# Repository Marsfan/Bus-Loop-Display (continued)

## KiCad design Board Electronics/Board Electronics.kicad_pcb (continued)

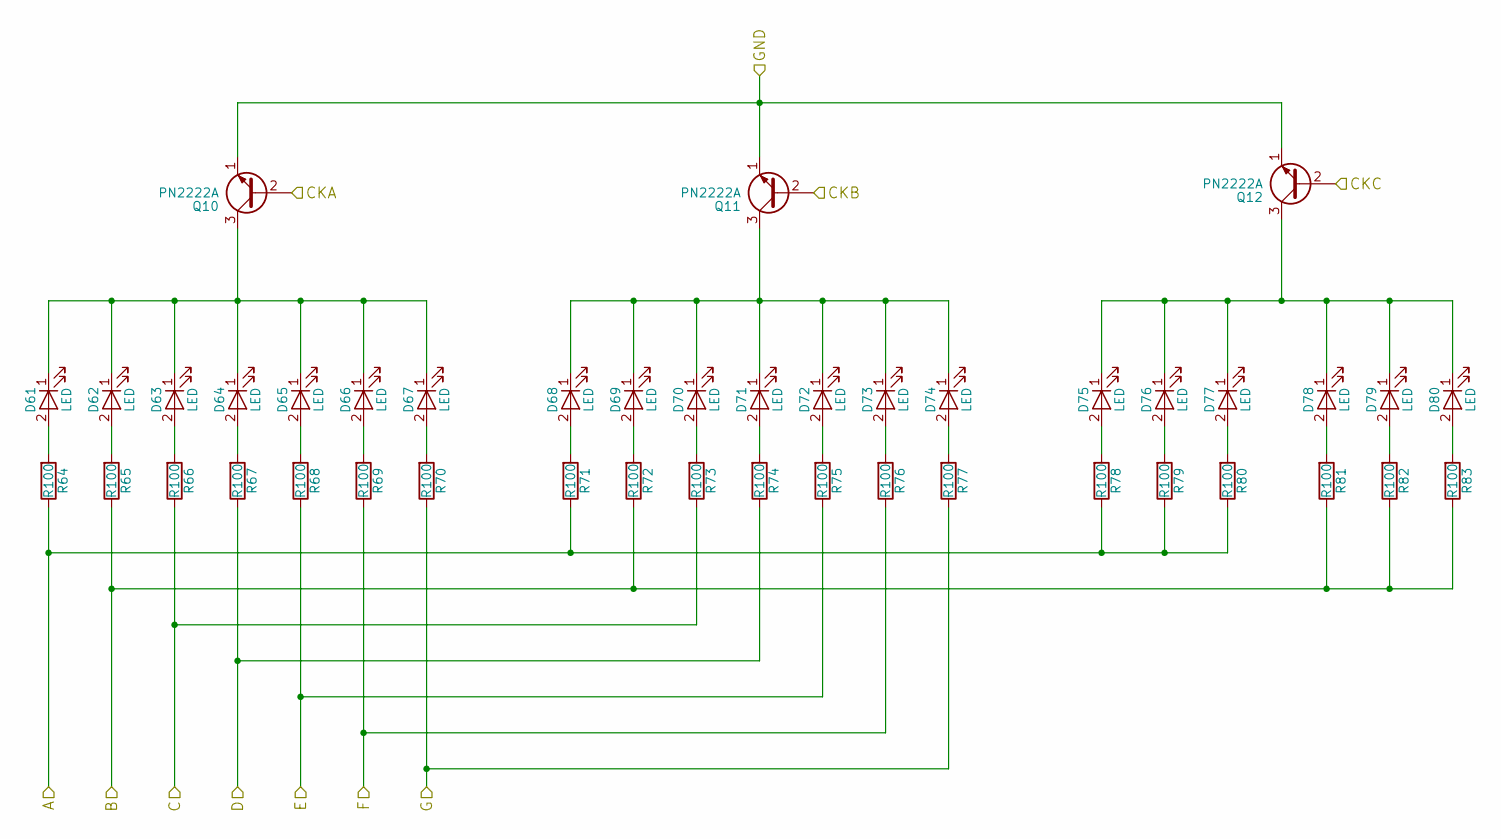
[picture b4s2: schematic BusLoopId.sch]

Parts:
D1, D2, D3, D4, D5, D6, D7, D8, D9, D10, D11, D12, D13, D14, D15, D16, D17, D18, D19, D20: LED; LED_D5.0mm
Q1, Q2, Q3: PN2222A; TO-92_Inline_Narrow_Oval
R4, R5, R6, R7, R8, R9, R10, R11, R12, R13, R14, R15, R16, R17, R18, R19, R20, R21, R22, R23: R100; R_Axial_DIN0309_L9.0mm_D3.2mm_P12.70mm_Horizontal

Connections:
/CKA: Q1.2 (B); also elsewhere on the board
/CKB: Q2.2 (B); also elsewhere on the board
/CKC: Q3.2 (B); also elsewhere on the board
/GND: Q1.1 (E), Q2.1 (E), Q3.1 (E); also elsewhere on the board
/Route 1/A: R4.1, R11.1, R18.1, R19.1, R20.1; also elsewhere on the board
/Route 1/B: R5.1, R12.1, R21.1, R22.1, R23.1; also elsewhere on the board
/Route 1/C: R6.1, R13.1; also elsewhere on the board
/Route 1/D: R7.1, R14.1; also elsewhere on the board
/Route 1/E: R8.1, R15.1; also elsewhere on the board
/Route 1/F: R9.1, R16.1; also elsewhere on the board
/Route 1/G: R10.1, R17.1; also elsewhere on the board
unnamed: D1.1 (K), D2.1 (K), D3.1 (K), D4.1 (K), D5.1 (K), D6.1 (K), D7.1 (K), Q1.3 (C)
unnamed: D1.2 (A), R4.2
unnamed: D2.2 (A), R5.2
unnamed: D3.2 (A), R6.2
unnamed: D4.2 (A), R7.2
unnamed: D5.2 (A), R8.2
unnamed: D6.2 (A), R9.2
unnamed: D7.2 (A), R10.2
unnamed: D8.2 (A), R11.2
unnamed: D9.2 (A), R12.2
unnamed: D8.1 (K), D9.1 (K), D10.1 (K), D11.1 (K), D12.1 (K), D13.1 (K), D14.1 (K), Q2.3 (C)
unnamed: D10.2 (A), R13.2
unnamed: D11.2 (A), R14.2
unnamed: D12.2 (A), R15.2
unnamed: D13.2 (A), R16.2
unnamed: D14.2 (A), R17.2
unnamed: D15.1 (K), D16.1 (K), D17.1 (K), D18.1 (K), D19.1 (K), D20.1 (K), Q3.3 (C)
unnamed: D15.2 (A), R18.2
unnamed: D16.2 (A), R19.2
unnamed: D17.2 (A), R20.2
unnamed: D18.2 (A), R21.2
unnamed: D19.2 (A), R22.2
unnamed: D20.2 (A), R23.2

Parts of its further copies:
D21, D22, D23, D24, D25, D26, D27, D28, D29, D30, D31, D32, D33, D34, D35, D36, D37, D38, D39, D40, D41, D42, D43, D44, D45, D46, D47, D48, D49, D50, D51, D52, D53, D54, D55, D56, D57, D58, D59, D60, D61, D62, D63, D64, D65, D66, D67, D68, D69, D70, D71, D72, D73, D74, D75, D76, D77, D78, D79, D80, D81, D82, D83, D84, D85, D86, D87, D88, D89, D90, D91, D92, D93, D94, D95, D96, D97, D98, D99, D100, D101, D102, D103, D104, D105, D106, D107, D108, D109, D110, D111, D112, D113, D114, D115, D116, D117, D118, D119, D120: LED; LED_D5.0mm
Q4, Q5, Q6, Q7, Q8, Q9, Q10, Q11, Q12, Q13, Q14, Q15, Q16, Q17, Q18: PN2222A; TO-92_Inline_Narrow_Oval
R24, R25, R26, R27, R28, R29, R30, R31, R32, R33, R34, R35, R36, R37, R38, R39, R40, R41, R42, R43, R44, R45, R46, R47, R48, R49, R50, R51, R52, R53, R54, R55, R56, R57, R58, R59, R60, R61, R62, R63, R64, R65, R66, R67, R68, R69, R70, R71, R72, R73, R74, R75, R76, R77, R78, R79, R80, R81, R82, R83, R84, R85, R86, R87, R88, R89, R90, R91, R92, R93, R94, R95, R96, R97, R98, R99, R100, R101, R102, R103, R104, R105, R106, R107, R108, R109, R110, R111, R112, R113, R114, R115, R116, R117, R118, R119, R120, R121, R122, R123: R100; R_Axial_DIN0309_L9.0mm_D3.2mm_P12.70mm_Horizontal

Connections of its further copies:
/CKA: Q4.2 (B), Q7.2 (B), Q10.2 (B), Q13.2 (B), Q16.2 (B); also elsewhere on the board
/CKB: Q5.2 (B), Q8.2 (B), Q11.2 (B), Q14.2 (B), Q17.2 (B); also elsewhere on the board
/CKC: Q6.2 (B), Q9.2 (B), Q12.2 (B), Q15.2 (B), Q18.2 (B); also elsewhere on the board
/GND: Q4.1 (E), Q5.1 (E), Q6.1 (E), Q7.1 (E), Q8.1 (E), Q9.1 (E), Q10.1 (E), Q11.1 (E), Q12.1 (E), Q13.1 (E), Q14.1 (E), Q15.1 (E), Q16.1 (E), Q17.1 (E), Q18.1 (E); also elsewhere on the board
/Route 2/A: R24.1, R31.1, R38.1, R39.1, R40.1; also elsewhere on the board
/Route 2/B: R25.1, R32.1, R41.1, R42.1, R43.1; also elsewhere on the board
/Route 2/C: R26.1, R33.1; also elsewhere on the board
/Route 2/D: R27.1, R34.1; also elsewhere on the board
/Route 2/E: R28.1, R35.1; also elsewhere on the board
/Route 2/F: R29.1, R36.1; also elsewhere on the board
/Route 2/G: R30.1, R37.1; also elsewhere on the board
/Route 3/A: R44.1, R51.1, R58.1, R59.1, R60.1; also elsewhere on the board
/Route 3/B: R45.1, R52.1, R61.1, R62.1, R63.1; also elsewhere on the board
/Route 3/C: R46.1, R53.1; also elsewhere on the board
/Route 3/D: R47.1, R54.1; also elsewhere on the board
/Route 3/E: R48.1, R55.1; also elsewhere on the board
/Route 3/F: R49.1, R56.1; also elsewhere on the board
/Route 3/G: R50.1, R57.1; also elsewhere on the board
/Route 4/A: R64.1, R71.1, R78.1, R79.1, R80.1; also elsewhere on the board
/Route 4/B: R65.1, R72.1, R81.1, R82.1, R83.1; also elsewhere on the board
/Route 4/C: R66.1, R73.1; also elsewhere on the board
/Route 4/D: R67.1, R74.1; also elsewhere on the board
/Route 4/E: R68.1, R75.1; also elsewhere on the board
/Route 4/F: R69.1, R76.1; also elsewhere on the board
/Route 4/G: R70.1, R77.1; also elsewhere on the board
/Route 5/A: R84.1, R91.1, R98.1, R99.1, R100.1; also elsewhere on the board
/Route 5/B: R85.1, R92.1, R101.1, R102.1, R103.1; also elsewhere on the board
/Route 5/C: R86.1, R93.1; also elsewhere on the board
/Route 5/D: R87.1, R94.1; also elsewhere on the board
/Route 5/E: R88.1, R95.1; also elsewhere on the board
/Route 5/F: R89.1, R96.1; also elsewhere on the board
/Route 5/G: R90.1, R97.1; also elsewhere on the board
/Route 6/A: R104.1, R111.1, R118.1, R119.1, R120.1; also elsewhere on the board
/Route 6/B: R105.1, R112.1, R121.1, R122.1, R123.1; also elsewhere on the board
/Route 6/C: R106.1, R113.1; also elsewhere on the board
/Route 6/D: R107.1, R114.1; also elsewhere on the board
/Route 6/E: R108.1, R115.1; also elsewhere on the board
/Route 6/F: R109.1, R116.1; also elsewhere on the board
/Route 6/G: R110.1, R117.1; also elsewhere on the board
unnamed: D21.1 (K), D22.1 (K), D23.1 (K), D24.1 (K), D25.1 (K), D26.1 (K), D27.1 (K), Q4.3 (C)
unnamed: D21.2 (A), R24.2
unnamed: D22.2 (A), R25.2
unnamed: D23.2 (A), R26.2
unnamed: D24.2 (A), R27.2
unnamed: D25.2 (A), R28.2
unnamed: D26.2 (A), R29.2
unnamed: D27.2 (A), R30.2
unnamed: D28.1 (K), D29.1 (K), D30.1 (K), D31.1 (K), D32.1 (K), D33.1 (K), D34.1 (K), Q5.3 (C)
unnamed: D28.2 (A), R31.2
unnamed: D29.2 (A), R32.2
unnamed: D30.2 (A), R33.2
unnamed: D31.2 (A), R34.2
unnamed: D32.2 (A), R35.2
unnamed: D33.2 (A), R36.2
unnamed: D34.2 (A), R37.2
unnamed: D35.1 (K), D36.1 (K), D37.1 (K), D38.1 (K), D39.1 (K), D40.1 (K), Q6.3 (C)
unnamed: D35.2 (A), R38.2
unnamed: D36.2 (A), R39.2
unnamed: D37.2 (A), R40.2
unnamed: D38.2 (A), R41.2
unnamed: D39.2 (A), R42.2
unnamed: D40.2 (A), R43.2
unnamed: D41.1 (K), D42.1 (K), D43.1 (K), D44.1 (K), D45.1 (K), D46.1 (K), D47.1 (K), Q7.3 (C)
unnamed: D41.2 (A), R44.2
unnamed: D42.2 (A), R45.2
unnamed: D43.2 (A), R46.2
unnamed: D44.2 (A), R47.2
unnamed: D45.2 (A), R48.2
unnamed: D46.2 (A), R49.2
unnamed: D47.2 (A), R50.2
unnamed: D48.1 (K), D49.1 (K), D50.1 (K), D51.1 (K), D52.1 (K), D53.1 (K), D54.1 (K), Q8.3 (C)
unnamed: D48.2 (A), R51.2
unnamed: D49.2 (A), R52.2
unnamed: D50.2 (A), R53.2
unnamed: D51.2 (A), R54.2
unnamed: D52.2 (A), R55.2
unnamed: D53.2 (A), R56.2
unnamed: D54.2 (A), R57.2
unnamed: D55.1 (K), D56.1 (K), D57.1 (K), D58.1 (K), D59.1 (K), D60.1 (K), Q9.3 (C)
unnamed: D55.2 (A), R58.2
unnamed: D56.2 (A), R59.2
unnamed: D57.2 (A), R60.2
unnamed: D58.2 (A), R61.2
unnamed: D59.2 (A), R62.2
unnamed: D60.2 (A), R63.2
unnamed: D61.1 (K), D62.1 (K), D63.1 (K), D64.1 (K), D65.1 (K), D66.1 (K), D67.1 (K), Q10.3 (C)
unnamed: D61.2 (A), R64.2
unnamed: D62.2 (A), R65.2
unnamed: D63.2 (A), R66.2
unnamed: D64.2 (A), R67.2
unnamed: D65.2 (A), R68.2
unnamed: D66.2 (A), R69.2
unnamed: D67.2 (A), R70.2
unnamed: D68.1 (K), D69.1 (K), D70.1 (K), D71.1 (K), D72.1 (K), D73.1 (K), D74.1 (K), Q11.3 (C)
unnamed: D68.2 (A), R71.2
unnamed: D69.2 (A), R72.2
unnamed: D70.2 (A), R73.2
unnamed: D71.2 (A), R74.2
unnamed: D72.2 (A), R75.2
unnamed: D73.2 (A), R76.2
unnamed: D74.2 (A), R77.2
unnamed: D75.1 (K), D76.1 (K), D77.1 (K), D78.1 (K), D79.1 (K), D80.1 (K), Q12.3 (C)
unnamed: D75.2 (A), R78.2
unnamed: D76.2 (A), R79.2
unnamed: D77.2 (A), R80.2
unnamed: D78.2 (A), R81.2
unnamed: D79.2 (A), R82.2
unnamed: D80.2 (A), R83.2
unnamed: D81.1 (K), D82.1 (K), D83.1 (K), D84.1 (K), D85.1 (K), D86.1 (K), D87.1 (K), Q13.3 (C)
unnamed: D81.2 (A), R84.2
unnamed: D82.2 (A), R85.2
unnamed: D83.2 (A), R86.2
unnamed: D84.2 (A), R87.2
unnamed: D85.2 (A), R88.2
unnamed: D86.2 (A), R89.2
unnamed: D87.2 (A), R90.2
unnamed: D88.1 (K), D89.1 (K), D90.1 (K), D91.1 (K), D92.1 (K), D93.1 (K), D94.1 (K), Q14.3 (C)
unnamed: D88.2 (A), R91.2
unnamed: D89.2 (A), R92.2
unnamed: D90.2 (A), R93.2
unnamed: D91.2 (A), R94.2
unnamed: D92.2 (A), R95.2
unnamed: D93.2 (A), R96.2
unnamed: D94.2 (A), R97.2
unnamed: D95.2 (A), R98.2
unnamed: D96.2 (A), R99.2
unnamed: D97.2 (A), R100.2
unnamed: D98.2 (A), R101.2
unnamed: D99.2 (A), R102.2
unnamed: D95.1 (K), D96.1 (K), D97.1 (K), D98.1 (K), D99.1 (K), D100.1 (K), Q15.3 (C)
unnamed: D100.2 (A), R103.2
unnamed: D101.1 (K), D102.1 (K), D103.1 (K), D104.1 (K), D105.1 (K), D106.1 (K), D107.1 (K), Q16.3 (C)
unnamed: D101.2 (A), R104.2
unnamed: D102.2 (A), R105.2
unnamed: D103.2 (A), R106.2
unnamed: D104.2 (A), R107.2
unnamed: D105.2 (A), R108.2
unnamed: D106.2 (A), R109.2
unnamed: D107.2 (A), R110.2
unnamed: D108.1 (K), D109.1 (K), D110.1 (K), D111.1 (K), D112.1 (K), D113.1 (K), D114.1 (K), Q17.3 (C)
unnamed: D108.2 (A), R111.2
unnamed: D109.2 (A), R112.2
unnamed: D110.2 (A), R113.2
unnamed: D111.2 (A), R114.2
unnamed: D112.2 (A), R115.2
unnamed: D113.2 (A), R116.2
unnamed: D114.2 (A), R117.2
unnamed: D115.1 (K), D116.1 (K), D117.1 (K), D118.1 (K), D119.1 (K), D120.1 (K), Q18.3 (C)
unnamed: D115.2 (A), R118.2
unnamed: D116.2 (A), R119.2
unnamed: D117.2 (A), R120.2
unnamed: D118.2 (A), R121.2
unnamed: D119.2 (A), R122.2
unnamed: D120.2 (A), R123.2

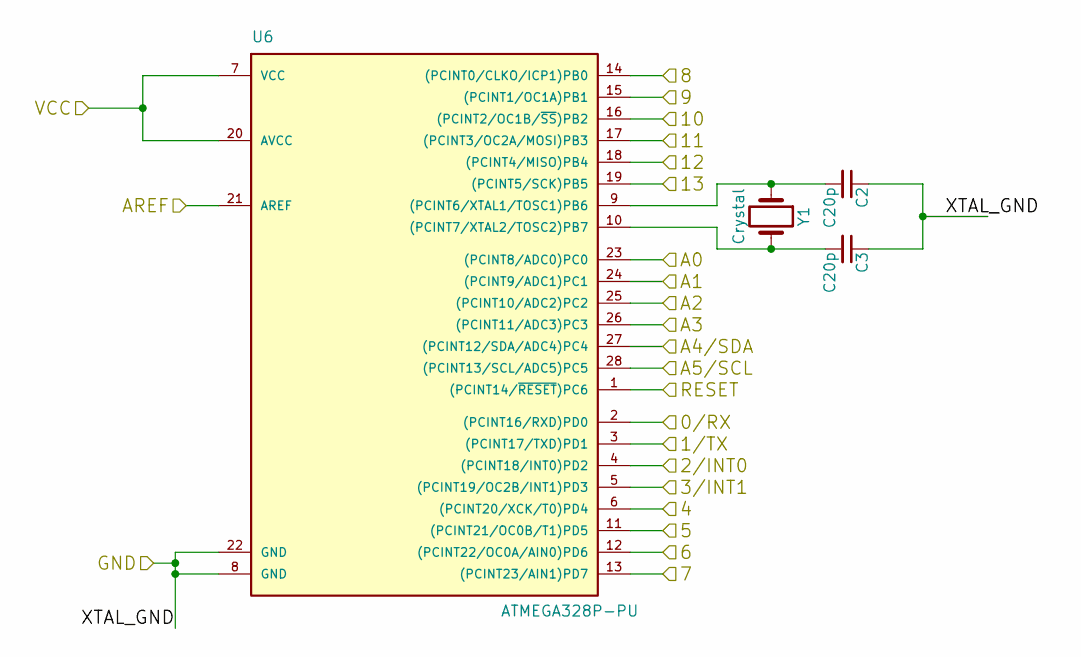
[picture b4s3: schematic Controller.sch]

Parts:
C2, C3: C20p; C_Disc_D6_P5
U6: ATMEGA328P-PU; DIP-28_W7.62mm_Socket
Y1: Crystal; Crystal_HC49-U_Vertical

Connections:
/7: U6.13 ((PCINT23/AIN1)PD7); also elsewhere on the board
/13: U6.19 ((PCINT5/SCK)PB5); also elsewhere on the board
/AREF: U6.21 (AREF); also elsewhere on the board
/CKA: U6.6 ((PCINT20/XCK/T0)PD4); also elsewhere on the board
/CKB: U6.11 ((PCINT21/OC0B/T1)PD5); also elsewhere on the board
/CKC: U6.12 ((PCINT22/OC0A/AIN0)PD6); also elsewhere on the board
/CTS: U6.17 ((PCINT3/OC2A/MOSI)PB3); also elsewhere on the board
/GND: C2.1, C3.1, U6.8 (GND), U6.22 (GND); also elsewhere on the board
/INT0: U6.4 ((PCINT18/INT0)PD2); also elsewhere on the board
/INT1: U6.5 ((PCINT19/OC2B/INT1)PD3); also elsewhere on the board
/MOD: U6.18 ((PCINT4/MISO)PB4); also elsewhere on the board
/RTS: U6.14 ((PCINT0/CLKO/ICP1)PB0); also elsewhere on the board
/RX: U6.2 ((PCINT16/RXD)PD0); also elsewhere on the board
/RXI: U6.15 ((PCINT1/OC1A)PB1); also elsewhere on the board
/SCL: U6.28 ((PCINT13/SCL/ADC5)PC5); also elsewhere on the board
/SDA: U6.27 ((PCINT12/SDA/ADC4)PC4); also elsewhere on the board
/TX: U6.3 ((PCINT17/TXD)PD1); also elsewhere on the board
/TXO: U6.16 ((PCINT2/OC1B/~SS~)PB2); also elsewhere on the board
/VCC: U6.7 (VCC), U6.20 (AVCC); also elsewhere on the board
/controller.sch/A0: U6.23 ((PCINT8/ADC0)PC0); also elsewhere on the board
/controller.sch/A1: U6.24 ((PCINT9/ADC1)PC1); also elsewhere on the board
/controller.sch/A2: U6.25 ((PCINT10/ADC2)PC2); also elsewhere on the board
/controller.sch/A3: U6.26 ((PCINT11/ADC3)PC3); also elsewhere on the board
/controller.sch/RESET: U6.1 ((PCINT14/~RESET~)PC6); also elsewhere on the board
unnamed: C2.2, U6.9 ((PCINT6/XTAL1/TOSC1)PB6), Y1.1
unnamed: C3.2, U6.10 ((PCINT7/XTAL2/TOSC2)PB7), Y1.2

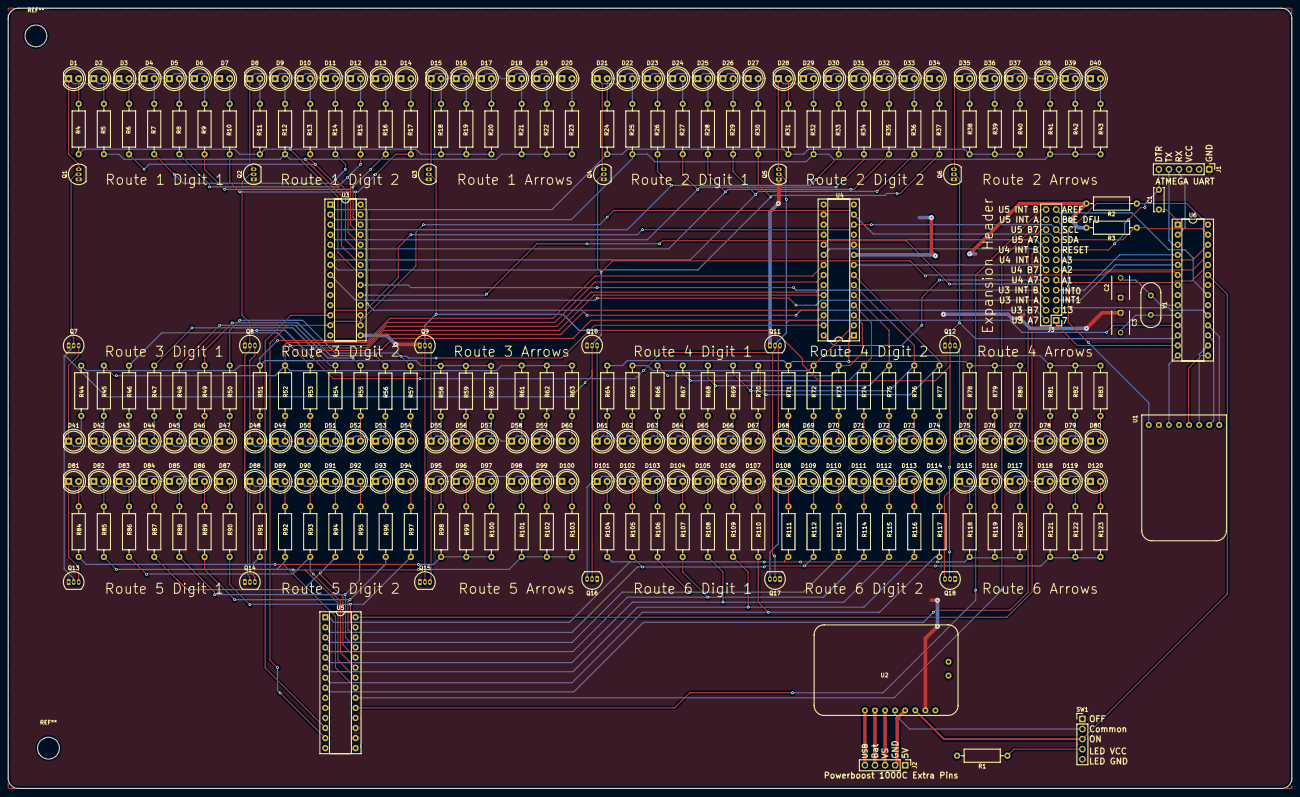
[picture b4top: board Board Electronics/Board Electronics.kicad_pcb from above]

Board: 2 copper layers, 323.9 x 196.9 mm, 275 parts (0 on the bottom side), 226 nets.

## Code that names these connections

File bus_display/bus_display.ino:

#include <Wire.h>             //i2c library, used to talk to MCP23017 Port expanders.
#include <SoftwareSerial.h>   //SoftwareSerial library, allows ATMEGA to talk to bluefruit port over pins other than 0 and 1, allowing for those to remain open for code editing. 

//Libraries used by the bluefruit module, this abstracts away talking to the bluefruit.
#include "Adafruit_BLE.h"
#include "Adafruit_BluefruitLE_UART.h"

#include "BluefruitConfig.h"  //Config file we set up. It should be tab 2 in this program, it contains a few simple settings for the bluefruit



//create bluefruit object. I have inlcuded HWSERIAL and SSERIAL Versions, Use comments to chose the mode you want.
//Software Serial allows for use while device is connected to computer over pins 0 and 1
//Hardware Serial is a bit more reliable
//adafruit says with the flow control pins, software serial is pretty reliable.


//Sofware Serial
SoftwareSerial bluefruitSS = SoftwareSerial(BLUEFRUIT_SWUART_TXD_PIN, BLUEFRUIT_SWUART_RXD_PIN); //Creates Software Serial on pins specified in header file


//declares bluetooth obect
Adafruit_BluefruitLE_UART ble(bluefruitSS, BLUEFRUIT_UART_MODE_PIN,
                              BLUEFRUIT_UART_CTS_PIN, BLUEFRUIT_UART_RTS_PIN);

//Hardware Serial
// Adafruit_BluefruitLE_UART ble(Serial1, BLUEFRUIT_UART_MODE_PIN);


//The digits and Arrows are written in Hex, because that is the most commonly used form for I2C transmission. They break down into binary as instruction on what LED segments should be lit up.
//                       0    1      2    3     4       5     6    7      8    9     -
const byte digits[] = {0x3f, 0x06, 0x5b, 0x4f, 0x66, 0x6d, 0x7d, 0x07, 0x7f, 0x6f, 0x00};
//off   left  right
const byte arrows[] = {0x07, 0x38};
//  1     2     3
const byte chips[] = {0x20, 0x21, 0x23};
//  A     B
const byte ports[] = {0x14, 0x15};

const int blinkTime = 1000;


float voltage;

byte bank[6][3] = {
  {digits[10], digits[10], digits[10]},  //digit 1
  {digits[10], digits[10], digits[10]},  //digit 2
  {digits[10], digits[10], digits[10]},  //digit 3

  {digits[10], digits[10], digits[10]},  //digit 4
  {digits[10], digits[10], digits[10]},  //digit 5
  {digits[10], digits[10], digits[10]},  //digit 6
};

String data = "";

const byte cka = 4;
const byte ckb = 5;
const byte ckc = 6;
boolean batWarn = false;

void setup() {
  pinMode(cka, OUTPUT);
  pinMode(ckb, OUTPUT);
  pinMode(ckc, OUTPUT);
  digitalWrite(cka, LOW);
  digitalWrite(ckb, LOW);
  digitalWrite(ckc, LOW);
  Wire.begin();         //set up i2c
  Serial.begin(115200); //set serial at 115200 baud, for high speed data transfer
  Serial.println(F("CHS Bus Loop Dispatch System Debug Terminal"));

  //set all pins on our i2c chips to output
  for (int i = 0; i < 3; i++) {
    Wire.beginTransmission(chips[i]);
    Wire.write(0x00);
    Wire.write(0x00);
    Wire.endTransmission();
    Wire.beginTransmission(chips[i]);
    Wire.write(0x01);
    Wire.write(0x00);
    Wire.endTransmission();

  }



  //initalize bluefruit, and select verbosity.
  if (!ble.begin(VERBOSE_MODE)) {
    error(F("Could not find Bluefruit, make it is wired and switch is in CMD"));
  }
  Serial.println( F("BLE Initialized!") );

  delay(1000);
  //if factory reset flagged, resets system
  if (FACTORYRESET_ENABLE) {
    Serial.println(F("Performing Factory Reset"));
    ble.sendCommandCheckOK("AT+GAPDEVNAME=" deviceName);
    if (!ble.factoryReset()) {
      error(F("Factory Reset Failed, this sometimes happens after uploading code"));
    }
  }
  
  
  ble.echo(false); //disables command echo from Bluefruit, reducing tx/rx times.
  ble.info(); //Display information about bluefruit over serial bus.
  ble.verbose(false); //debug info gets annoying, remove if something is really wonky.



  //Wait for connection
  while (!ble.isConnected()) {
    delay(500);
  }

  //set up LED mode. this is only supported on firmware 0.6.6 and up,
  //so we need to check it first

  if (ble.isVersionAtLeast(MINIMUM_FIRMWARE_VERSION)) {
    ble.sendCommandCheckOK("AT+HWModeLED=" MODE_LED_BEHAVIOUR);
    Serial.println(F("set led to " MODE_LED_BEHAVIOUR));
  }


  //Set module to DATA Mode, so the chip acts as a serial passthrough

  Serial.println(F("Switching to DATA Mode"));
  ble.setMode(BLUEFRUIT_MODE_DATA);

}

void loop() {
  if (ble.available()) {
    getMsg();
  }
  digitalWrite(cka, HIGH);
  blinkChips(bank[0][0], bank[1][0], bank[2][0], bank[3][0], bank[4][0], bank[5][0]);
  digitalWrite(cka, LOW);
  digitalWrite(ckb, HIGH);
  blinkChips(bank[0][1], bank[1][1], bank[2][1], bank[3][1], bank[4][1], bank[5][1]);
  digitalWrite(ckb, LOW);
  digitalWrite(ckc, HIGH);
  blinkChips(bank[0][2], bank[1][2], bank[2][2], bank[3][2], bank[4][2], bank[5][2]);
  digitalWrite(ckc, LOW);
  voltage = analogRead(0);
  voltage = mapFloat(voltage, 0, 1023, 0, 5);
  /* if(voltage < 3.4 && !batWarn){
     ble.print(F("Low Battery"));
     batWarn = true;
    }*/
}

void splitMsg(String msg) {
  //split message into 2 longs, so it can hold this data
  unsigned long first = msg.substring(0, 9).toInt();
  unsigned long last = msg.substring(9).toInt();
  //write values to bank using first and last variables
  Serial.println(F("New Digit Values"));
  unsigned long divisor = 100000000;                                     //set a divisor to find the first digit
  for (int x = 0; x < 3; x++) {                                           //loop through the first three banks
    for (int y = 0; y < 3; y++) {                                         //loop through the three digits per bank
      if (y == 2) {
        bank[x][y] = arrows[(first / divisor) % 10];

      } else {
        bank[x][y] = digits[(first / divisor) % 10];                        //find the value that should go in this digit
      }
      divisor = divisor / 10;                                             //divide the divisor, so next time we get the next digit.
    }
  }
  //do the same as above, but with the last three banks
  divisor = 100000000;
  for (int x = 3; x < 6; x++) {
    for (int y = 0; y < 3; y++) {
      if (y == 2) {
        bank[x][y] = arrows[(last / divisor) % 10];
      } else {
        bank[x][y] = digits[(last / divisor) % 10];
      }
      divisor = divisor / 10;
    }
  }
  for (int i = 0; i < 6; i++) {
    for (int q = 0; q < 3; q++) {

      Serial.print(bank[i][q], HEX);
      Serial.print("  ");
      if (q == 2) {
        Serial.println("");
      }
    }
  }

}



void getMsg() {
  data = "";
  while (ble.available()) {
    int c = ble.read();
    data.concat((char)c);
  }
  Serial.println(F("Message Recieved"));
  Serial.println(F("Raw Message"));
  splitMsg(data);

}

void blinkChips(byte a1, byte b1, byte a2, byte b2, byte a3, byte b3) {
  writeChip(chips[0], ports[0], a1);
  writeChip(chips[1], ports[0], a2);
  writeChip(chips[2], ports[0], a3);
  delayMicroseconds(blinkTime);
  writeChip(chips[0], ports[0], 0);
  writeChip(chips[1], ports[0], 0);
  writeChip(chips[2], ports[0], 0);

  writeChip(chips[0], ports[1], b1);
  writeChip(chips[1], ports[1], b2);
  writeChip(chips[2], ports[1], b3);
  delayMicroseconds(blinkTime);
  writeChip(chips[0], ports[1], 0);
  writeChip(chips[1], ports[1], 0);
  writeChip(chips[2], ports[1], 0);

}

void writeChip(byte chip, byte reg, byte data) {
  Wire.beginTransmission(chip);
  Wire.write(reg);
  Wire.write(data);
  Wire.endTransmission();
}

// A small helper for throwing initialization errors.

void error(const __FlashStringHelper*err) {
  Serial.println(err);
  while (1);
}

float mapFloat(long x, long in_min, long in_max, long out_min, long out_max)
{
  return (float)(x - in_min) * (out_max - out_min) / (float)(in_max - in_min) + out_min;
}

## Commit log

2017-03-06 :octocat: Added .gitattributes & .gitignore files
2017-03-06 add arduino and electronic schematics
2017-03-09 Finished Single Board PCB Design
2017-03-09 Finished Arduino Code
2017-03-09 added copper pours
2017-03-24 update Kicad files to have new schematic design
    This new schematic design is nested under a new folder called
    alternative board electronics. It breaks apart the control circuitry and
    the led attachment points to save PCB space (and this cost).
    This may become the default schematics in a future revision, and the
    all-in-one board will become the alternative.
2017-03-24 added low battery warning, changed arrows hex values
2017-04-04 First Addition of Code
    Some bluetooth messing around with, but the UI is here in its primal
    form
2017-04-13 New bluetooth build
    First version suspected to completely work
2017-04-13 cleaning up the git repo
2017-04-13 Button Positions now stay the same based on platform/rotation
2017-04-18 4-18-17
    Fixed Scanner, Found Low Bluetooth but Sending data is an issue
2017-04-19 4-19-17
    Keyboard dismisses itself when tapping out
2017-04-22 Fix send message?
    This should fix the sending message bugs we are having, we did not properly associate charactersitic variables (I think). It should now match the UUID with the known services and add them to their re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
    Data from: [https://stackoverflow.com/questions/32170456/what-does-fatal-error-unexpectedly-found-nil-while-unwrapping-an-optional-valu](https://stackoverflow.com/questions/32170456/what-does-fatal-e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
2017-04-24 4-24-17
    Gabe Edits
2017-04-24 Some tweaks by game
2017-04-24 Message is now sending
2017-04-25 4-23-17
    All Working Code
2017-05-10 FIxed an error with B registers not working properly
2017-05-10 rework a lot of things to make it work better
2017-05-10 add copper pour
2017-05-12 more tweaking for perfection
2017-06-11 just some more tweaks
2017-06-20 Add ATNotes and ATCOMMAND script
2018-07-01 Some Tweaks I never pushed
2018-07-29 Fix for libraries
2018-11-01 Upgraded control board schematic to KiCad V5
